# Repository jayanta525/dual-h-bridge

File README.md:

### Personal Project

2021

# Dual H Bridge Controller with N-CH MOSFETS

- IRF3205 N Channel MOSFET
- IR2104 MOSFET Driver
- ATMega328P-AU PWM Generator

#### Made for Dual 250W Brushed wheelchair motor
#### Schematics: https://jayanta525.gitlab.io/dual-h-bridge/sch/
#### Schematics: https://jayanta525.github.io/dual-h-bridge/sch/

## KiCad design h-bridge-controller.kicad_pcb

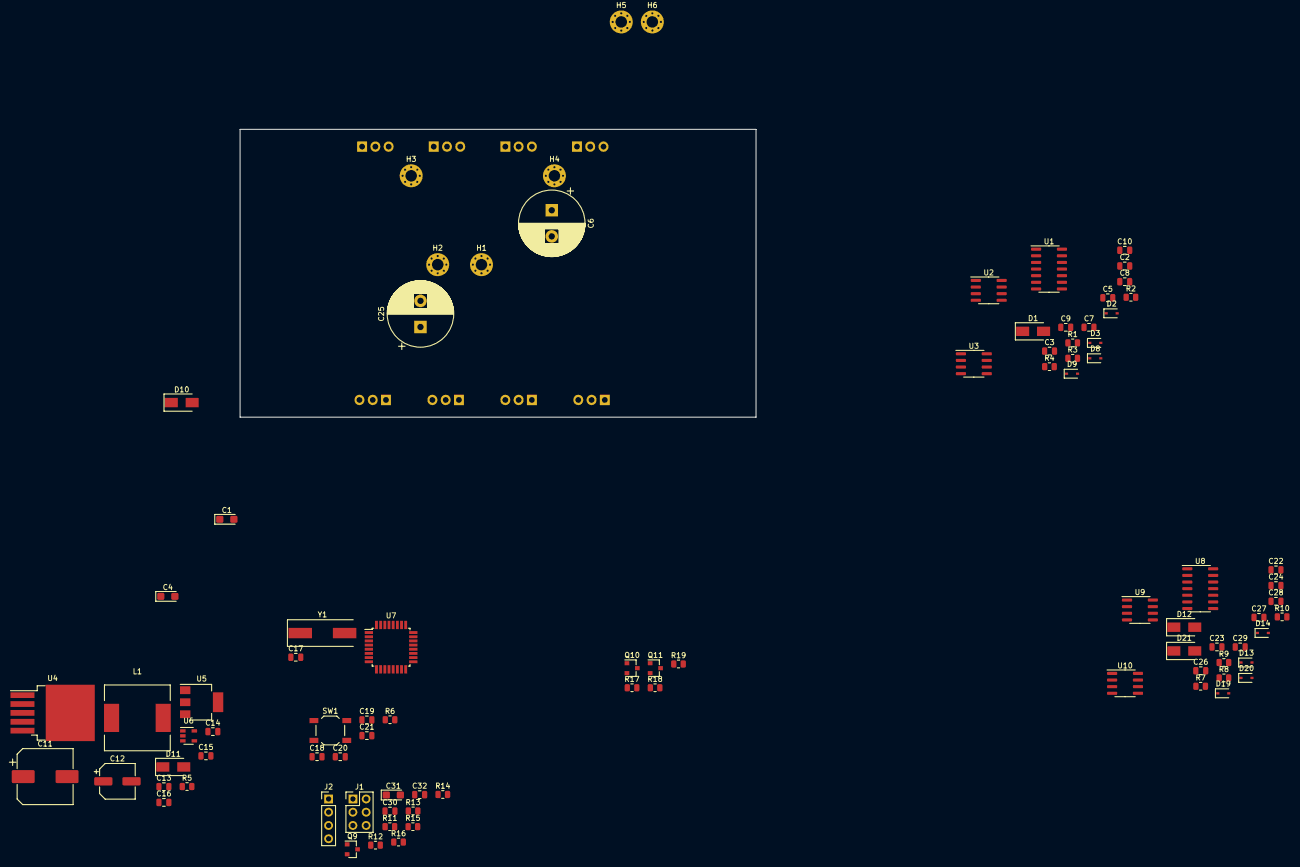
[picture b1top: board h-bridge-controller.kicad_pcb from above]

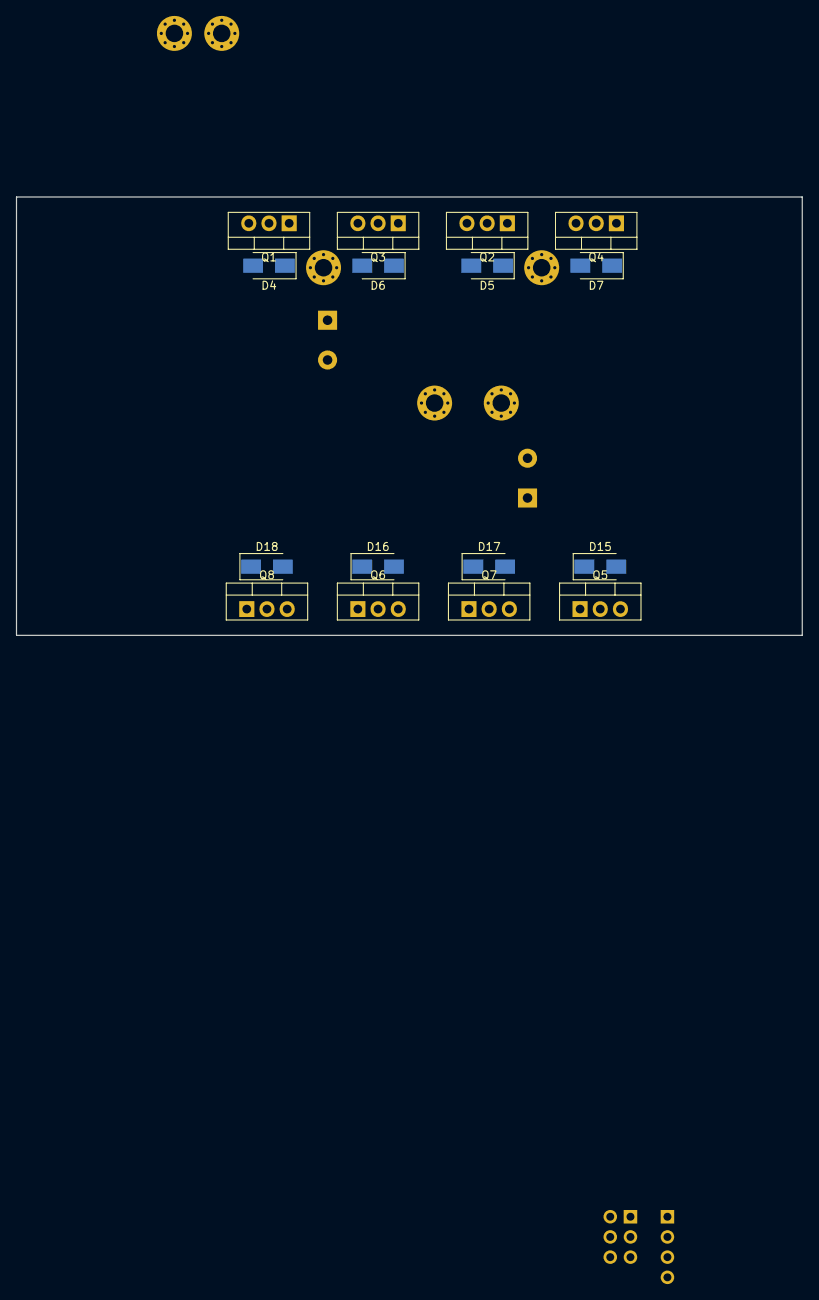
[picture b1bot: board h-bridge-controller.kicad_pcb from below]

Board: 2 copper layers, 98.8 x 55.1 mm, 104 parts (16 on the bottom side), 59 nets, no tracks yet.

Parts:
C1, C4, C31: 10uF; CP_EIA-3216-18_Kemet-A
C2, C5, C9, C22, C24, C28: 1uF; C_0805_2012Metric
C3, C10, C19, C20, C21, C23, C29, C30, C32: 0.1uF; C_0805_2012Metric
C6, C25: 1000uF/35V; CP_Radial_D12.5mm_P5.00mm
C7, C8, C26, C27: 470nF; C_0805_2012Metric
C11: 220uF/50V; CP_Elec_10x10.5
C12: 220uF/16V; CP_Elec_6.3x7.7
C13, C14, C16: 10uF; C_0805_2012Metric
C15: 470pF; C_0805_2012Metric
C17, C18: 22pF; C_0805_2012Metric
D1, D10, D12, D21: SS14; D_SMA
D2, D3, D8, D9, D13, D14, D19, D20: 1N4148WS; D_SOD-323
D4, D5, D6, D7, D15, D16, D17, D18: SS24; D_SMA
D11: SS34; D_SMA
H1, H2, H3, H4, H5, H6: MountingHole_Pad; MountingHole_2.2mm_M2_Pad_Via
J1: Conn_02x03_Odd_Even; PinHeader_2x03_P2.54mm_Vertical
J2: Conn_01x04; PinHeader_1x04_P2.54mm_Vertical
L1: 33uH; L_12x12mm_H4.5mm
Q1, Q2, Q3, Q4, Q5, Q6, Q7, Q8: IRF3205; TO-220-3_Vertical
Q9: BSS84; SOT-23
Q10: BSS138; SOT-23
Q11: AO3401A; SOT-23
R1, R2, R3, R4, R7, R8, R9, R10: 27R; R_0805_2012Metric
R5: 100K; R_0805_2012Metric
R6, R11, R12, R13, R17, R18, R19: 10K; R_0805_2012Metric
R14: 1K; R_0805_2012Metric
R15: 390K; R_0805_2012Metric
R16: 91K; R_0805_2012Metric
SW1: RST; SW_SPST_TL3342
U1, U8: 74LS02; SOIC-14_3.9x8.7mm_P1.27mm
U2, U3, U9, U10: IR2104; SOIC-8_3.9x4.9mm_P1.27mm
U4: LM2596S-12; TO-263-5_TabPin3
U5: AMS1117-5.0; SOT-223-3_TabPin2
U6: MIC5219-3.3YM5; SOT-23-5
U7: ATmega328P-AU; TQFP-32_7x7mm_P0.8mm
Y1: 16MHz; Crystal_SMD_HC49-SD

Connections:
3V3_EN: R5.2, U6.3, U7.11
+3V3: C16.1, U6.5
+5V: C2.1, C14.1, C21.1, C22.1, C30.1, C31.1, J1.5, R6.1, R11.1, R12.1, U1.14, U5.2, U7.4, U7.6, U7.18, U8.14
+12V: C1.1, C3.1, C4.1, C10.1, C12.1, C13.1, C23.1, C29.1, D1.2, D10.2, D12.2, D21.2, L1.2, U2.1, U3.1, U4.4, U5.3, U6.1, U9.1, U10.1
+24V: C6.1, C7.1, C8.1, C11.1, C25.1, C26.1, C27.1, D4.1, D6.1, D15.1, D17.1, H1.1, Q1.2, Q3.2, Q5.2, Q7.2, R13.1, R15.1, U4.1
/ATMega328P/A0: C32.1, Q9.3, R16.1, U7.23
/ATMega328P/BAT_READ_EN: R14.1, U7.14
/ATMega328P/DTR: C19.2, J2.2
/ATMega328P/MISO: J1.6, U7.16
/ATMega328P/MOSI: J1.3, U7.15
/ATMega328P/RESET: C19.1, J1.2, R6.2, SW1.2, U7.29
/ATMega328P/RXD: J2.4, U7.30
/ATMega328P/SCK: J1.4, U7.17
/ATMega328P/TXD: J2.3, U7.31
/ATMega328P/XTAL1: C17.1, U7.7, Y1.1
/ATMega328P/XTAL2: C18.1, U7.8, Y1.2
/H-Bridge-left/EN1: U8.13, U9.3, U10.3
/H-Bridge-left/MOTOR-A: C24.2, D15.2, D16.1, H5.1, Q5.3, Q6.2, U9.6
/H-Bridge-left/MOTOR-B: C28.2, D17.2, D18.1, H6.1, Q7.3, Q8.2, U10.6
/H-Bridge-left/PWM1: U8.4, U9.2
/H-Bridge-left/PWM2: U8.10, U10.2
/H-Bridge-right/EN1: U1.13, U2.3, U3.3
/H-Bridge-right/MOTOR-A: C5.2, D4.2, D5.1, H3.1, Q1.3, Q2.2, U2.6
/H-Bridge-right/MOTOR-B: C9.2, D6.2, D7.1, H4.1, Q3.3, Q4.2, U3.6
/H-Bridge-right/PWM1: U1.4, U2.2
/H-Bridge-right/PWM2: U1.10, U3.2
DIRECTION-L: U7.2, U8.2, U8.3, U8.9
DIRECTION-R: U1.2, U1.3, U1.9, U7.9
ENABLE-L: R12.2, U7.13, U8.11
ENABLE-R: R11.2, U1.11, U7.12
GNDREF: C1.2, C2.2, C3.2, C4.2, C6.2, C7.2, C8.2, C10.2, C11.2, C12.2, C13.2, C14.2, C15.2, C16.2, C17.2, C18.2, C20.2, C21.2, C22.2, C23.2, C25.2, C26.2, C27.2, C29.2, C30.2, C31.2, C32.2, D5.2, D7.2, D11.2, D16.2, D18.2, H2.1, J1.1, J2.1, Q2.3, Q4.3, Q6.3, Q8.3, R5.1, R16.2, SW1.1, U1.7, U1.12, U2.4, U3.4, U4.3, U4.5, U5.1, U6.2, U7.3, U7.5, U7.21, U8.7, U8.12, U9.4, U10.4
unnamed: C5.1, D1.1, U2.8
unnamed: C9.1, D10.1, U3.8
unnamed: C15.1, U6.4
unnamed: C20.1, U7.20
unnamed: C24.1, D12.1, U9.8
unnamed: C28.1, D21.1, U10.8
unnamed: D2.1, R1.2, U2.7
unnamed: D2.2, Q1.1, R1.1
unnamed: D3.1, R2.2, U2.5
unnamed: D3.2, Q2.1, R2.1
unnamed: D8.1, R3.2, U3.7
unnamed: D8.2, Q3.1, R3.1
unnamed: D9.1, R4.2, U3.5
unnamed: D9.2, Q4.1, R4.1
unnamed: D11.1, L1.1, U4.2
unnamed: D13.1, R7.2, U9.7
unnamed: D13.2, Q5.1, R7.1
unnamed: D14.1, R8.2, U9.5
unnamed: D14.2, Q6.1, R8.1
unnamed: D19.1, R9.2, U10.7
unnamed: D19.2, Q7.1, R9.1
unnamed: D20.1, R10.2, U10.5
unnamed: D20.2, Q8.1, R10.1
unnamed: Q9.1, R13.2, R14.2
unnamed: Q9.2, R15.2
unnamed: U1.1, U1.5
unnamed: U8.1, U8.5
PWM: U1.6, U1.8, U7.10, U8.6, U8.8

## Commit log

2021-12-21 init project
2021-12-21 Add LICENSE
2021-12-21 Add README.md
2021-12-22 add svg
2021-12-22 fix names
2021-12-22 add pages ci
2021-12-22 fix multi-page
2021-12-23 add bootsrap styling to multi-page
2021-12-23 add 404
2021-12-28 update to kicad6<< revert this
2021-12-31 add github pages
2022-01-16 Revert "update to kicad6<< revert this"
    This reverts commit 94c354bf1f03422d884be196bd183532f7be4acb.
